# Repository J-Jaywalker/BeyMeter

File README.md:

# BeyBeetle (WIP)

The BeyBeetle is a custom tool used to measure the angle and RPM of beyblade launches. This repo contains instructions and resources to create a BeyBeetle of your own!

## Design Philosophy

The BeyBeetle is built from easily available, commercial-off-the-shelf (COTS) hardware, so that it can easily be assambled by people who have limited tools, knowledge, resources and space. Even the 3D printed chasis and bill of materials (BOM) are easily aquired through online printing services and hardware vendors. 

All the code and instructions on how to compile, as well as links to recently compiled and up-to-date .uf2 files are included here, so that enthusiasts of all walks are able to build a BeyBeetle should they want to. 

Why a Beetle? I like beetles, they are one of my favourite animals and my other projects feature them as well. 

## What it does

The BeyBeetle reads launch angle from an IMU strapped to your launcher, and will read rotational speed from an IR interrupt sensor once that part is done. On boot it runs a splash while it checks the display, the IMU and the battery gauge, then drops you straight into the bubble screen — there's no menu to fight your way through.

**The bubble screen** is a spirit level for your launcher. Concentric rings mark 15°, 30° and 45° off-axis, and an orange dot moves in real time as you tilt — think of it like a crosshair you're trying to keep centred. Floating beside the dot are your pitch and roll in degrees, each with a little arrow pointing the way you need to correct. Readings are smoothed with an exponential moving average so the display doesn't jitter, and a small battery icon in the corner keeps an eye on charge level so you're not caught out mid-session.

**Locking in** happens through the micro switch the beyblade presses against when it's seated in the launcher. Hold it down and the screen arms itself — the corner crosses spin into place and ARMED tape scrolls down the left edge and along the bottom, so you can tell at a glance that the meter is watching.

**Launching** is just letting go. The instant the beyblade leaves, a green mark drops at exactly the angle you were holding — it flickers for a second, twists from a + into an X, and settles with the angle numbers alongside it. Arm up for your next shot and that mark greys out but stays put, so you can chase the same angle again when the last launch was a good one. Only the previous launch is kept, and it lives behind the live dot so it never gets in the way.

**Sleep** kicks in after three minutes without anything locked in. The screen blanks, the sensors power down and the RP2040 goes fully dormant — no reading, no calculating, nothing. Hold the lock switch for three seconds and it wakes up and boots from scratch, checks and all. Worth knowing: the display's backlight is wired permanently on, so until I run a wire to a spare pin, sleep saves a lot less power than it ought to.

## Roadmap

Launch detection is done — the micro switch catches the moment the beyblade leaves, so the angle that gets recorded is the angle at the point of release rather than whatever you happened to be holding a second beforehand. Everything below builds on that.

**1. RPM mode**
The IR sensor has a home on the board but nothing in the firmware reads it yet. The goal is a reliable launch RPM logged alongside the angle you already get. This is the headline feature and it'll get done properly rather than rushed.

**2. Stats and recall**
Right now the meter remembers your last launch and nothing else, and even that goes when you power it down. Once RPM is in, the records worth keeping — top shoot speed, total launch count — go into flash so they survive a power cycle, with a screen to show them off.

**3. Polish and wrap-up**
The final stretch — finishing the 3D printed chassis, running the backlight wire so sleep actually saves the battery it's meant to, tightening up the UI, and general improvements that come out of actually using the thing in the field.

## First-time setup

Open WSL and run these steps:

**1. Install the toolchain**
```bash
sudo apt install cmake gcc-arm-none-eabi libnewlib-arm-none-eabi build-essential
```

**2. Clone the Pico SDK**
```bash
git clone https://github.com/raspberrypi/pico-sdk ~/pico-sdk
cd ~/pico-sdk && git submodule update --init
echo 'export PICO_SDK_PATH=~/pico-sdk' >> ~/.bashrc && source ~/.bashrc
```

**3. Clone the libraries**
```bash
cd ~/BeyMeter
mkdir lib
git clone https://github.com/libdriver/st7789 lib/st7789
git clone https://github.com/STMicroelectronics/ism330dhcx-pid lib/ism330dhcx-pid
```

That's it — you only need to do this once.

## Every day usage

From `~/BeyMeter`:

```bash
make uf2    # clean build → BeyMeter.uf2
make hex    # clean build → BeyMeter.hex
make build  # incremental build (faster, no clean)
make clean  # wipe build artifacts
```

## Flashing

1. Hold **BOOTSEL** on the Feather and plug it into USB
2. It appears as a drive called `RPI-RP2` in Windows Explorer
3. Drag `BeyMeter.uf2` onto the drive — it reboots automatically

## Previewing the screens

Both stdio outputs are switched off in `CMakeLists.txt`, so there's no serial to watch — turn `pico_enable_stdio_usb` back on if you need it for debugging.

If you just want to see the screens without flashing anything, open [`tools/sim.html`](tools/sim.html) in a browser. It's a reimplementation of the display in JavaScript at the same 240x240, with the mouse aiming the launcher and buttons for the lock switch and the rip cord, so you can watch the arming animation and the launch mark without picking up a beyblade. It doesn't sync itself with the firmware, so if you change how something is drawn in `src/screens.c`, change it there too.

## Hardware

| Component | Connection | Purpose |
|-----------|------------|------------|
| Adafruit Feather RP2040 | — | Main board |
| ISM330DHCX IMU | STEMMA QT (I2C) | Tilt and pitch angle measurement |
| MAX17048 LiPo fuel gauge | STEMMA QT (I2C) | Battery management |
| TRCT5000 IR sensor | GPIO | RPM measurement (not read by the firmware yet) |
| D2F micro switch | GPIO |  Beyblde "lock-in" detection |
| Adafruit EyeSPI | SPI | Enables FFC cable connection |
| Adafruit 4313 1.3" 240x240 TFT IPS display | EyeSPI | Display |

Full bill of materials in [`bom/`](bom/).

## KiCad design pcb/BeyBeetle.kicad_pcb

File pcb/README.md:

# BeyBeetle carrier board

KiCad 9 project for the board everything plugs into. It's a motherboard rather
than a proper PCBA — every module is an Adafruit breakout sitting in a
through-hole female header, so nothing is soldered down permanently and any part
can be pulled and replaced.

Board as ordered: 80mm x 60mm, 1.6mm FR4, lead-free HASL, 1oz copper, all
through-hole at 2.54mm pitch, ground plane on B.Cu. First run went to JLCPCB on
2026-06-19.

## What's in here

| Path | What it is |
|------|------------|
| `BeyBeetle.kicad_pro` | Project file — open this one |
| `BeyBeetle.kicad_sch` | Schematic |
| `BeyBeetle.kicad_pcb` | Board layout |

The `.kicad_prl`, `fp-info-cache` and `BeyBeetle-backups/` are all gitignored —
KiCad regenerates them and they're either huge or specific to whoever's machine
the project was last opened on.

## Getting boards made

No gerbers here — roll your own from the files above so you know they match the
board you're looking at, and so you can tweak it first if you want to. In KiCad:
File → Fabrication Outputs → Gerbers, then Drill Files, then zip the folder and
upload that. Most fabs are happy with KiCad's defaults. Mine came from JLCPCB
with the spec at the top of this page.

## Connectors

Every connection is documented in the schematic, but the short version:

| Ref | Module |
|-----|--------|
| J1, J2 | Feather RP2040 (16-pin left, 12-pin right) |
| J3 | MAX17048 fuel gauge |
| J4 | ISM330DHCX IMU (I2C side) |
| J5, J6 | EyeSPI breakout (top and bottom rows) |
| J7 | D2F lock switch |
| J8 | TCRT5000 IR sensor |

One thing to fix on the next revision: EyeSPI `LITE` is a no-connect, so the
display backlight is permanently on and the firmware's sleep mode can't switch
it off. It wants routing to a spare GPIO — 27 (A1) is free.

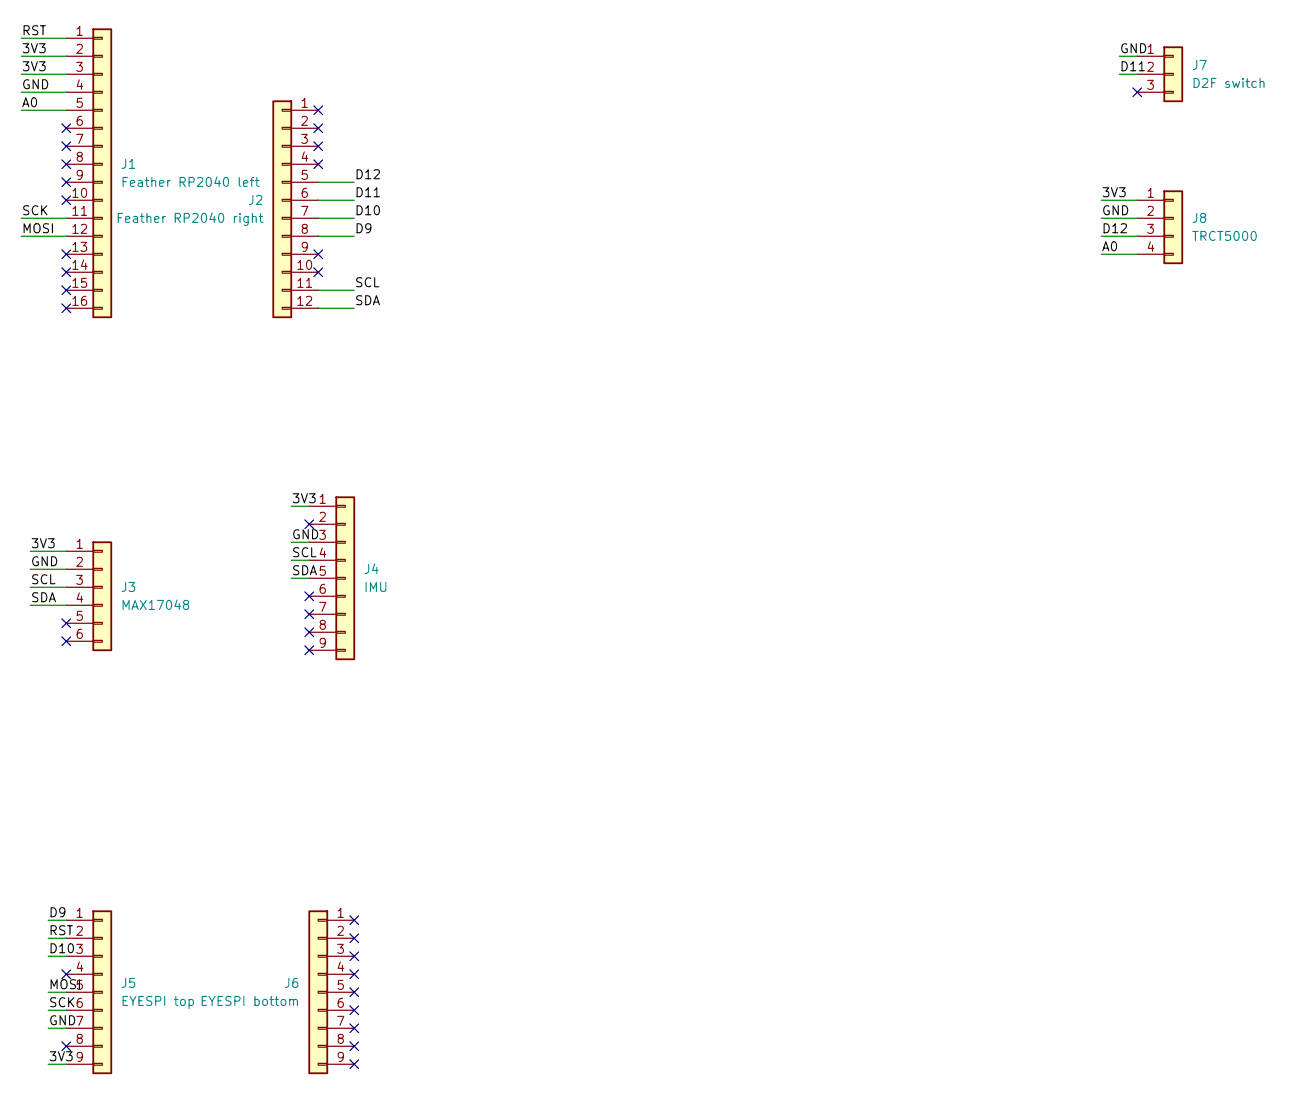
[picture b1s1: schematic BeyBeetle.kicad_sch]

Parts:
J1: Feather RP2040 left; PinHeader_1x16_P2.54mm_Vertical
J2: Feather RP2040 right; PinHeader_1x12_P2.54mm_Vertical
J3: MAX17048; PinHeader_1x06_P2.54mm_Vertical
J4: IMU; PinHeader_1x09_P2.54mm_Vertical
J5: EYESPI top; PinHeader_1x09_P2.54mm_Vertical
J6: EYESPI bottom; PinHeader_1x09_P2.54mm_Vertical
J7: D2F switch; PinHeader_1x03_P2.54mm_Vertical
J8: TRCT5000; PinHeader_1x04_P2.54mm_Vertical

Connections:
/3V3: J1.2, J1.3, J3.1, J4.1, J5.9, J8.1
/A0: J1.5, J8.4
/D9: J2.8, J5.1
/D10: J2.7, J5.3
/D11: J2.6, J7.2
/D12: J2.5, J8.3
/GND: J1.4, J3.2, J4.3, J5.7, J7.1, J8.2
/MOSI: J1.12, J5.5
/RST: J1.1, J5.2
/SCK: J1.11, J5.6
/SCL: J2.11, J3.3, J4.4
/SDA: J2.12, J3.4, J4.5

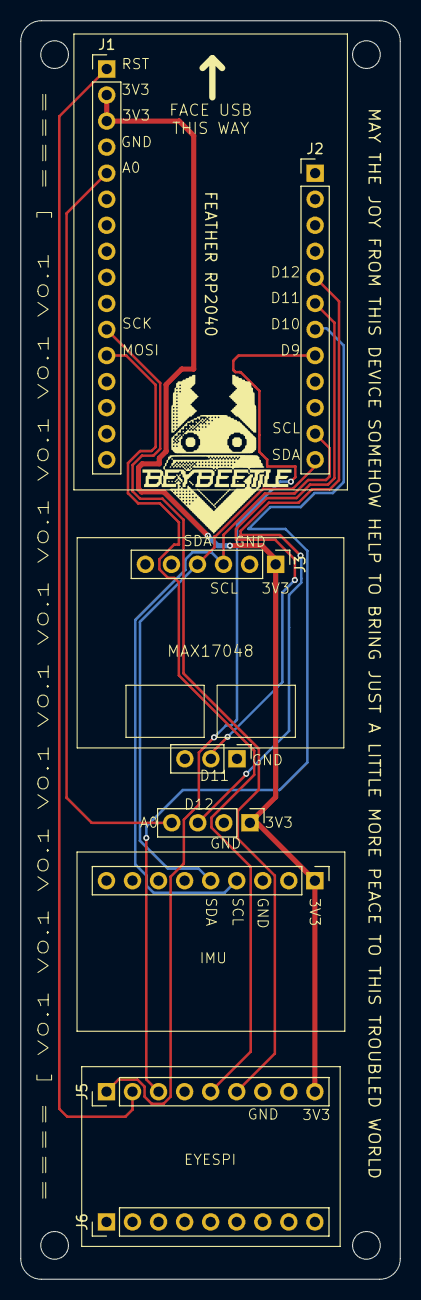
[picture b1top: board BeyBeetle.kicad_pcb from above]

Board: 2 copper layers, 37.0 x 122.7 mm, 12 parts (0 on the bottom side), 12 nets.

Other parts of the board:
BL_MOUNT: MountingHole_2.7mm
BR_MOUNT: MountingHole_2.7mm
TL_MOUNT: MountingHole_2.7mm
TR_MOUNT: MountingHole_2.7mm

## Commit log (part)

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2026-04-26 simplify readme
2026-04-26 First pass of IMU functionality
2026-04-26 update makefile and readme for imu
2026-04-26 remove old circuitpython poc
2026-04-26 add bubble mode
2026-04-28 add rings to bubble mode, change to rectangles
2026-04-29 improved menu
2026-04-29 update menu, readme
2026-04-29 fix readme
2026-05-01 add roadmap
2026-05-11 add bom, new enclosure, update readme and roadmap
2026-05-11 fix splash
